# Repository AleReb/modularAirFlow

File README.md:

# Modular Air Flow

Sistema modular para **generar, medir y dirigir flujo de aire**, con **ESP32-S3 en la central y en todos los módulos adicionales**.

La central reúne el **sensor de flujo AFM3000**, el **control del motor/ventilador** y la interfaz de usuario. Todos los sensores extra y actuadores externos se incorporan como módulos esclavos al **segundo I2C**. El primer módulo conectado es el **minirevolver**, que controla localmente su motor paso a paso y su final de carrera.

## 1. Idea del sistema

La central mide el caudal, permite ajustar el PWM del ventilador y envía órdenes a los módulos. Cada módulo tiene su propio ESP32-S3, ejecuta su función y entrega su estado cuando la central lo consulta.

- **Central:** AFM3000, ventilador, interfaz de usuario y coordinación.
- **Minirevolver:** movimiento, búsqueda de origen y reporte de posición/estado.
- **Módulos adicionales:** sensores extra o actuadores con funciones y direcciones propias.

La interfaz actual es el monitor USB serial. Una pantalla, controles físicos o una interfaz web quedan por definir. El firmware actual permite ajustar el PWM manualmente y leer el flujo; el control automático de caudal todavía no está implementado.

```mermaid
flowchart TB
    U["Usuario: monitor USB serial"] <--> C["Central ESP32-S3\nFlujo, control del ventilador y coordinación"]
    C <-->|"Primer I2C: SDA6 / SCL7"| N["Conversor I2C 3,3 V / 5 V"]
    N <--> A["AFM3000 local\nDirección 0x40"]
    C -->|"Control y PWM"| B["BTS7960"]
    B --> V["Motor / ventilador"]
    C <-->|"Segundo I2C: SDA8 / SCL9"| R["Minirevolver ESP32-S3\nEsclavo 0x30"]
    C <-->|"Mismo segundo I2C"| X["Sensores extra y actuadores\nMódulos esclavos ESP32-S3 futuros"]
    R -->|"STEP / DIR"| D["Driver del motor paso a paso"]
    D --> M["Motor del revólver"]
    H["Final de carrera HOME"] --> R
```

El AFM3000 y el ventilador permanecen integrados en la central. El motor del revólver es un actuador distinto y lo controla el módulo minirevolver.

## 2. Los dos buses I2C

Esta es la asignación de pines del proyecto. El firmware configura los GPIO explícitamente; los pines predeterminados de la placa seleccionada en Arduino IDE pueden ser otros.

| Bus | Controlador | SDA | SCL | Uso |
| --- | --- | --- | --- | --- |
| Primer I2C | `TwoWire(0)` | **GPIO6** | **GPIO7** | AFM3000 y periféricos locales de la central |
| Segundo I2C | `TwoWire(1)` | **GPIO8** | **GPIO9** | Control y consulta de todos los módulos externos |

En ambos buses de la central, la central inicia las transacciones. En el segundo bus, los módulos trabajan como **esclavos**: reciben órdenes y responden a las consultas. Todos comparten las mismas líneas SDA, SCL y GND, con una dirección distinta por módulo.

El minirevolver usa también su segundo controlador, `TwoWire(1)`, con SDA8/SCL9 en modo esclavo. Su primer I2C queda reservado en GPIO6/7 y no se inicializa en el sketch actual.

**Los buses son independientes:** no unir SDA del primer bus con SDA del segundo ni sus líneas SCL. Las placas y periféricos comparten la referencia GND.

| Bus de la central | Dirección | Dispositivo | Estado |
| --- | --- | --- | --- |
| Primer I2C | `0x40` | AFM3000 local | Lectura implementada |
| Segundo I2C | `0x30` | Minirevolver ESP32-S3 | Órdenes y respuestas implementadas; pendiente de prueba en hardware |
| Segundo I2C | `0x31`, `0x32` | Posibles módulos futuros | Direcciones de ejemplo; firmware pendiente |

## 3. Conexiones de la central ESP32-S3

### Sensor de flujo AFM3000: primer I2C

El AFM3000 utiliza alimentación de **5 V**. SDA y SCL pasan por un **conversor bidireccional para I2C de 3,3 V a 5 V**, como en el montaje de flujo anterior.

| Central / alimentación | Conversor de nivel | AFM3000 |
| --- | --- | --- |
| GPIO6, SDA del primer I2C | SDA lado 3,3 V → SDA lado 5 V | SDA |
| GPIO7, SCL del primer I2C | SCL lado 3,3 V → SCL lado 5 V | SCL |
| 3,3 V | Referencia LV | — |
| 5 V | Referencia HV | VCC, 5 V |
| GND común | GND | GND |

```mermaid
flowchart LR
    subgraph CENTRAL["Central ESP32-S3: primer I2C"]
        SDA0["GPIO6 · SDA"]
        SCL0["GPIO7 · SCL"]
        LV["3,3 V"]
    end
    subgraph NIVEL["Conversor bidireccional I2C"]
        SDAL["SDA · lado LV"] <--> SDAH["SDA · lado HV"]
        SCLL["SCL · lado LV"] <--> SCLH["SCL · lado HV"]
        REF["Referencias: LV 3,3 V / HV 5 V"]
    end
    subgraph SENSOR["AFM3000 · 0x40"]
        SDAS["SDA"]
        SCLS["SCL"]
        VCC["VCC · 5 V"]
    end
    SDA0 <--> SDAL
    SCL0 <--> SCLL
    SDAH <--> SDAS
    SCLH <--> SCLS
    LV --- REF
    P5["Alimentación 5 V"] --- REF
    P5 --- VCC
    G["GND común: central, conversor y sensor"]
```

Los nombres de los canales del conversor pueden variar según la placa. La tabla describe las señales; verificar el pinout del sensor y del conversor utilizados. Cada lado del conversor lleva sus pull-ups a su tensión correspondiente.

### Motor/ventilador local: BTS7960

| Central ESP32-S3 | Señal del BTS7960 | Función en el firmware |
| --- | --- | --- |
| GPIO4 | R_EN | Habilitación |
| GPIO5 | L_EN | Habilitación |
| GPIO10 | RPWM | Se mantiene en LOW |
| GPIO11 | LPWM | PWM manual, de 0 a 255 |
| GND | GND de control | Referencia común |

```mermaid
flowchart LR
    subgraph C["Central ESP32-S3"]
        P4["GPIO4"]
        P5["GPIO5"]
        P10["GPIO10"]
        P11["GPIO11"]
    end
    subgraph B["BTS7960"]
        RE["R_EN"]
        LE["L_EN"]
        RP["RPWM · LOW"]
        LP["LPWM · PWM"]
        POT["Etapa de potencia"]
    end
    P4 --> RE
    P5 --> LE
    P10 --> RP
    P11 --> LP
    F["Fuente de potencia del motor"] --> POT
    POT --> M["Motor / ventilador"]
    G["GND de control común: central y driver"]
```

La tabla fija las señales de control. La alimentación lógica y de potencia del BTS7960 y las conexiones del motor se realizan según el módulo y motor utilizados. El motor recibe alimentación a través del driver.

**Cambio de cableado:** GPIO6/7 quedan reservados para el primer I2C. Las señales RPWM/LPWM que antes ocupaban esos pines pasan a GPIO10/11.

## 4. Conexión del minirevolver: segundo I2C

### Enlace entre la central y los módulos

| Señal | Central ESP32-S3 | Minirevolver ESP32-S3 |
| --- | --- | --- |
| SDA del segundo I2C | **GPIO8** | **GPIO8** |
| SCL del segundo I2C | **GPIO9** | **GPIO9** |
| Referencia | **GND** | **GND** |

Los siguientes módulos se conectan en paralelo a esas mismas señales. Cada módulo recibe su alimentación por una conexión definida aparte.

```text
Central ESP32-S3       Minirevolver S3       Módulo S3 extra
                      esclavo 0x30          dirección propia

GPIO8 · SDA ────────── GPIO8 · SDA ────────── GPIO8 · SDA

GPIO9 · SCL ────────── GPIO9 · SCL ────────── GPIO9 · SCL

GND ───────────────── GND ───────────────── GND

Pull-ups del bus: SDA → 3,3 V y SCL → 3,3 V.
```

El diagrama representa **tres redes separadas**: SDA, SCL y GND. Para evitar confusiones al cablear, seguir la tabla GPIO8↔GPIO8, GPIO9↔GPIO9 y GND↔GND.

El bus de módulos funciona a **100 kHz**, con señales de **3,3 V**. Para el montaje inicial, usar cables cortos y un par de pull-ups de **4,7 kΩ a 3,3 V** como punto de partida. Revisar las resistencias presentes en las placas: las pull-ups se combinan en paralelo.

Conector de señales propuesto: **1 GND, 2 SDA, 3 GND, 4 SCL**. La numeración es una propuesta del proyecto, no un pinout universal de conectores.

### Motor y final de carrera del minirevolver

| Minirevolver ESP32-S3 | Conexión | Función |
| --- | --- | --- |
| GPIO5 | STEP del driver | Pulsos del motor |
| GPIO10 | DIR del driver | Sentido de giro |
| GPIO11 | Contacto HOME | Final de carrera, `INPUT_PULLUP`, activo LOW |
| GND | Otro contacto del switch HOME | Contacto normalmente abierto hacia GND |
| GND | GND de control del driver | Referencia común |
| GPIO6 / GPIO7 | Primer I2C reservado | Sin inicializar en este sketch |

```mermaid
flowchart LR
    subgraph R["Minirevolver ESP32-S3"]
        STEP["GPIO5 · STEP"]
        DIR["GPIO10 · DIR"]
        HOME["GPIO11 · HOME\nINPUT_PULLUP"]
    end
    STEP --> DS["STEP del driver"]
    DIR --> DD["DIR del driver"]
    DS --> D["Driver del motor paso a paso"]
    DD --> D
    F["Fuente de potencia"] --> D
    D --> M["Motor del revólver"]
    HOME --- SW["Switch HOME\nNormalmente abierto"]
    SW --- G["GND común"]
```

DIR y HOME pasan a GPIO10/11 para liberar GPIO6/7. Los GPIO pertenecen a cada placa: GPIO5 de la central y GPIO5 del revólver son señales independientes. El driver determina corriente y micropasos; el sketch no maneja un pin ENABLE.

La posición informada es un conteo de pasos enviados, sin encoder. El módulo arranca sin mover y exige completar la búsqueda de origen antes de aceptar posiciones absolutas. Los límites del ejemplo deben ajustarse a la mecánica.

## 5. Cómo se comunican

La central envía una orden a `0x30`. El minirevolver la procesa en su bucle, ejecuta el movimiento y publica una instantánea de estado. La central consulta periódicamente esa respuesta, incluso durante el movimiento.

```mermaid
sequenceDiagram
    participant U as Usuario
    participant C as Central ESP32-S3
    participant R as Minirevolver esclavo 0x30
    U->>C: REV HOME o REV POS 1
    C->>R: Orden por segundo I2C
    R->>R: Procesar orden y generar pasos localmente
    loop Consulta periódica mientras se mueve
        C->>R: Solicitar estado
        R-->>C: Secuencia, resultado, posición y flags
        C-->>U: Mostrar estado por USB
    end
    R->>R: Finalizar movimiento y actualizar estado
    C->>R: Solicitar estado
    R-->>C: Estado actualizado: movimiento terminado
```

Una orden recibida no significa que el movimiento haya terminado. La central muestra `moviendo`, `homing`, `origen` y `resultado`. El protocolo usa órdenes de **10 bytes** y respuestas de **14 bytes**, con secuencia y CRC8. La especificación está en [sistemasI2C/README.md](sistemasI2C/README.md#protocolo-versión-1).

Si no hay confirmación en 2 segundos, la central informa que la ejecución es incierta y no reenvía automáticamente la orden. Si se pierde el enlace, un movimiento ya aceptado continúa localmente hasta su destino o límite de búsqueda; no hay watchdog de comunicación.

## 6. Firmware y comandos

Cada carpeta con un `.ino` es un **sketch independiente**. Cargar en cada placa únicamente el sketch correspondiente, junto con sus headers.

| Placa | Sketch | Preparación |
| --- | --- | --- |
| Central ESP32-S3 | [centralI2C.ino](centralI2C/centralI2C.ino) | Arduino-ESP32 2.0.17, USB nativo y USB CDC On Boot activado |
| Minirevolver ESP32-S3 | [minirevolveri2c.ino](minirevolveri2c/minirevolveri2c.ino) | ESP_FlexyStepper; USB CDC On Boot para leer el diagnóstico por USB nativo |

Abrir el monitor de la central a **115200**, con terminación **Nueva línea** o **Ambos NL y CR**.

| Comando | Acción |
| --- | --- |
| `PWM 128` | Ajustar el PWM del ventilador local a 128/255; admite 0..255 |
| `STOP` | Apagar solamente el ventilador |
| `REV HOME` | Buscar el origen del revólver |
| `REV POS 1` | Solicitar destino absoluto de 150 pasos |
| `REV POS 2` | Solicitar destino absoluto de 350 pasos |
| `REV POS 3` | Solicitar destino absoluto de 550 pasos |
| `REV MOVE 160` | Solicitar destino absoluto de 160 pasos; admite 0..2000 |
| `REV STOP` | Pedir parada del revólver |
| `ESTADO` | Mostrar flujo, PWM y estado del revólver |
| `AYUDA` | Mostrar los comandos disponibles |

Las posiciones y el límite de 2000 pasos son provisionales. Esperar `origen: 1` después de `REV HOME` antes de solicitar posiciones. El ventilador arranca apagado y el revólver no se mueve al encender las placas.

## 7. Estado del proyecto y pruebas

La arquitectura central + minirevolver tiene firmware preparado, pero **está pendiente de compilación y prueba en hardware por el usuario**. El modelo concreto de placa S3 y los conectores todavía deben elegirse; comprobar que la placa exponga los GPIO asignados y que no estén ocupados por componentes propios.

Primera integración:

1. Revisar alimentación y cableado, incluidos los cambios de pines del motor.
2. Cargar los sketches correspondientes en la central y el minirevolver.
3. Consultar `ESTADO` y verificar la respuesta del módulo y el cambio del switch HOME al accionarlo.
4. Ejecutar `REV HOME` y comprobar el sentido físico de búsqueda y el límite mecánico.
5. Con `origen: 1`, probar una posición y consultar el estado durante el movimiento.
6. Probar `PWM n`, observar el flujo y usar `STOP` para apagar el ventilador.

Los módulos extra todavía requieren firmware propio y ampliar la central para consultar sus direcciones. Para extender el cableado, verificar capacitancia, flancos y ruido; RS-485 o CAN son alternativas futuras para enlaces de metros, sin implementación actual.

### Resultados anteriores del montaje de flujo

Estas observaciones corresponden al montaje probado anteriormente en ESP32-C3, según lo informado por el usuario. No constituyen una validación del nuevo firmware S3.

| Observación | Alcance |
| --- | --- |
| Flujo aproximado de 2 a 35 slm | Rango observado con ese ventilador y montaje |
| Puede no arrancar con PWM 160 y mantenerse a ese valor después de arrancar | Umbrales de arranque y marcha diferentes |
| Se detiene cerca de PWM 60 al reducir la orden | Valor aproximado observado; sin límite automático aplicado |
| Referencia de 1,8 slpm frente a lecturas AFM3000 de 1,90 a 2,30 slm | Diferencia pendiente de estudiar; sin corrección de calibración |

`slm` expresa litros estándar por minuto. El manual disponible del AFM3000 usa 20 °C y 1013 mbar. Confirmar las condiciones estándar al comparar con otro equipo. El sensor compensa internamente la temperatura; el manual disponible no documenta un comando para leerla.

El control automático de flujo, el impulso de arranque, un mínimo automático de marcha y una corrección de calibración quedan pendientes. Las ideas anteriores de PWM 255 durante 300 ms y mínimo 70 no están validadas ni implementadas.

## 8. Organización del repositorio

| Carpeta | Contenido |
| --- | --- |
| [centralI2C](centralI2C/README.md) | Central S3: flujo, PWM, dos buses y órdenes a módulos |
| [minirevolveri2c](minirevolveri2c/README.md) | Revólver S3 como esclavo en el segundo I2C |
| [sistemasI2C](sistemasI2C/README.md) | Detalles del enlace, cableado y protocolo versión 1 |
| [ventiladorFlujo](ventiladorFlujo/README.md) | Prueba anterior de PWM y AFM3000 en ESP32-C3, funcionamiento confirmado |
| [airSensor](airSensor/README.md) | Prueba aislada del sensor y manual PDF, lecturas confirmadas |
| [pruebaPWM](pruebaPWM/README.md) | Prueba anterior de analogWrite en GPIO9 de ESP32-C3 |
| [ventilador](ventilador/README.md) | Prueba anterior de rampas del puente en ambos sentidos |
| [minirevolver](minirevolver/README.md) | Control original por serial; pines anteriores 5/23/27 |

Los sketches anteriores se conservan como referencias funcionales. Sus pines y placas corresponden a esos montajes; seguir las tablas de este README para la arquitectura nueva.

## 9. Reglas de trabajo

Por indicación del usuario, el asistente **no debe compilar ni cargar firmware**. Las verificaciones del asistente son revisiones de código, documentación y archivos; las pruebas físicas confirmadas son las comunicadas por el usuario.

Guardar sketches y headers como UTF-8 **sin BOM**. Mantener idénticas las copias de `Protocolo.h` de central y minirevolver. Conservar las pruebas funcionales anteriores al desarrollar nuevas versiones.

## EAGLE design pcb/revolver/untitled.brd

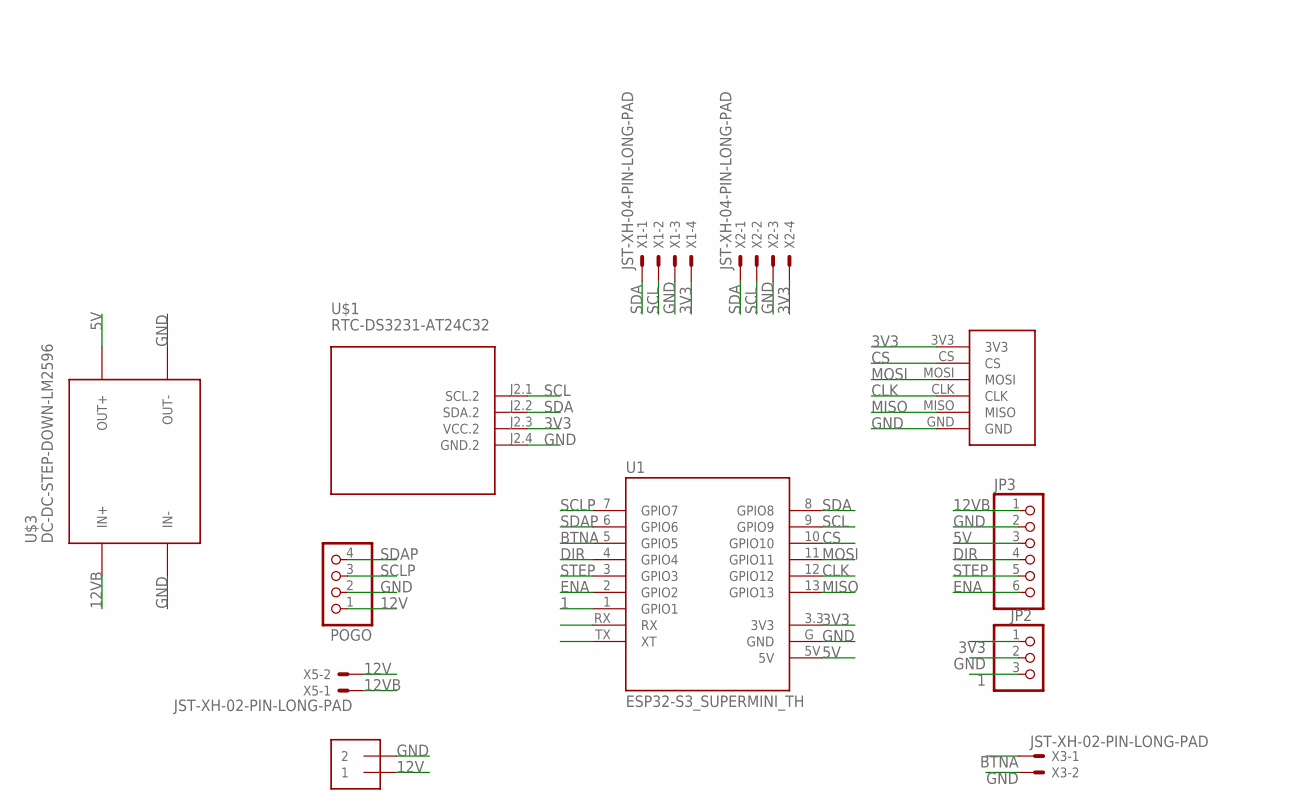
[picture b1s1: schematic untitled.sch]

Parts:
J1: 1X2-3.5MM
JP2: PINHD-1X3; 1X03
JP3: PINHD-1X6; 1X06
POGO: PINHD-1X4; 1X04
U1: ESP32-S3_SUPERMINI_TH; MODULE_ESP32-S3_SUPERMINI_TH
U$1: RTC-DS3231-AT24C32
U$2: SD_KUSKALLA
U$3: DC-DC-STEP-DOWN-LM2596
X1, X2: JST-XH-04-PIN-LONG-PAD; JST-XH-04-PACKAGE-LONG-PAD
X3, X5: JST-XH-02-PIN-LONG-PAD; JST-XH-02-PACKAGE-LONG-PAD

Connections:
1: JP2.3, U1.1 (GPIO1)
3V3: JP2.1, U1.3.3 (3V3), U$1.J2.3 (VCC.2), U$2.3V3, X1.4, X2.4
5V: JP3.3, U1.5V, U$3.OUT+
12V: J1.1, POGO.1, X5.2
12VB: JP3.1, U$3.IN+, X5.1
BTNA: U1.5 (GPIO5), X3.1
CLK: U1.12 (GPIO12), U$2.CLK
CS: U1.10 (GPIO10), U$2.CS
DIR: JP3.4, U1.4 (GPIO4)
ENA: JP3.6, U1.2 (GPIO2)
GND: J1.2, JP2.2, JP3.2, POGO.2, U1.G (GND), U$1.J2.4 (GND.2), U$2.GND, U$3.IN-, U$3.OUT-, X1.3, X2.3, X3.2
MISO: U1.13 (GPIO13), U$2.MISO
MOSI: U1.11 (GPIO11), U$2.MOSI
SCL: U1.9 (GPIO9), U$1.J2.1 (SCL.2), X1.2, X2.2
SCLP: POGO.3, U1.7 (GPIO7)
SDA: U1.8 (GPIO8), U$1.J2.2 (SDA.2), X1.1, X2.1
SDAP: POGO.4, U1.6 (GPIO6)
STEP: JP3.5, U1.3 (GPIO3)

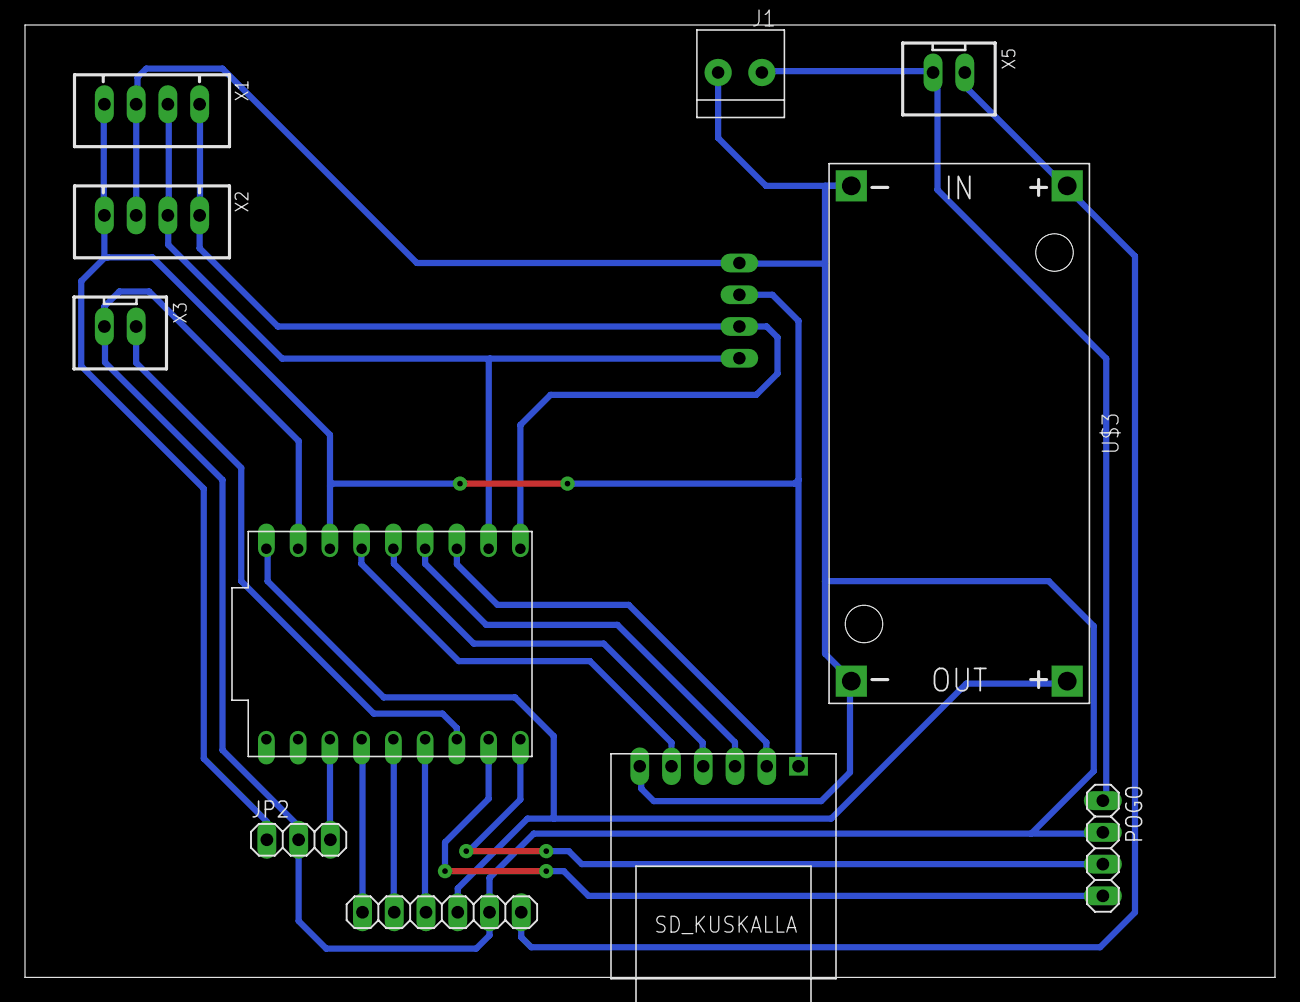
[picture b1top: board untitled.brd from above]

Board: 2 copper layers, 100.0 x 76.2 mm, 12 parts (1 on the bottom side), 18 nets.

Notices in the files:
parts and their libraries:
diy-modules: Released under the Creative Commons Attribution 4.0 International License: http://creativecommons.org/licenses/by/4.0
